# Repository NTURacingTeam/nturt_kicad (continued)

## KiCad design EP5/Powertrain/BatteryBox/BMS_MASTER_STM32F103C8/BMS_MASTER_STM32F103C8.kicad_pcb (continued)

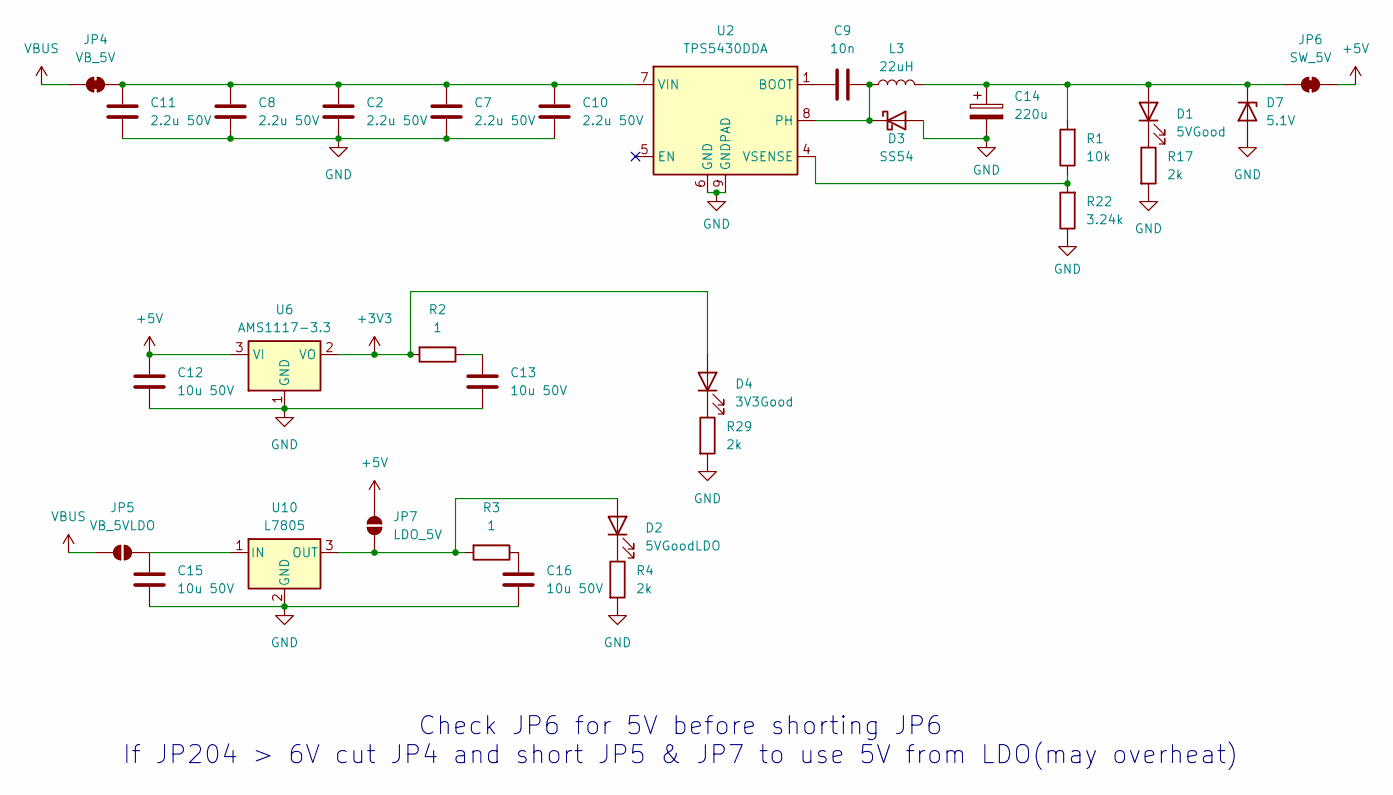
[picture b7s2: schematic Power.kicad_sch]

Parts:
C2, C7, C8, C10, C11: 2.2u 50V; C_0805_2012Metric
C9: 10n; C_0603_1608Metric
C12, C13, C15, C16: 10u 50V; C_1206_3216Metric
C14: 220u; CP_Elec_8x10.5
D1: 5VGood; LED_0603_1608Metric
D2: 5VGoodLDO; LED_0603_1608Metric
D3: SS54; D_SMA
D4: 3V3Good; LED_0603_1608Metric
D7: 5.1V; D_SOD-123
JP4: VB_5V; SolderJumper-2_P1.3mm_Bridged_Pad1.0x1.5mm
JP5: VB_5VLDO; SolderJumper-2_P1.3mm_Open_Pad1.0x1.5mm
JP6: SW_5V; SolderJumper-2_P1.3mm_Open_Pad1.0x1.5mm
JP7: LDO_5V; SolderJumper-2_P1.3mm_Open_Pad1.0x1.5mm
L3: 22uH; L_Bourns_SRR1260
R1: 10k; R_0603_1608Metric
R2, R3: 1; R_1206_3216Metric
R4, R17, R29: 2k; R_0603_1608Metric
R22: 3.24k; R_0603_1608Metric
U2: TPS5430DDA; TI_SO-PowerPAD-8_ThermalVias
U6: AMS1117-3.3; SOT-223-3_TabPin2
U10: L7805; TO-252-2

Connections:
3V3_REF: D4.2 (A), R2.2, U6.2 (VO); also elsewhere on the board
+5V: C12.1, JP6.2 (B), JP7.2 (B), U6.3 (VI); also elsewhere on the board
GND: C2.2, C7.2, C8.2, C10.2, C11.2, C12.2, C13.2, C14.2, C15.2, C16.2, D3.2 (A), D7.2 (A), R4.2, R17.2, R22.1, R29.2, U2.6 (GND), U2.9 (GNDPAD), U6.1 (GND), U10.2 (GND); also elsewhere on the board
unnamed: C13.1, R2.1
unnamed: C16.1, R3.1
unnamed: C14.1, D1.2 (A), D7.1 (K), JP6.1 (A), L3.2, R1.2
unnamed: D1.1 (K), R17.1
unnamed: D2.2 (A), JP7.1 (A), R3.2, U10.3 (OUT)
unnamed: D2.1 (K), R4.1
unnamed: C9.2, D3.1 (K), L3.1, U2.8 (PH)
unnamed: D4.1 (K), R29.1
unnamed: C2.1, C7.1, C8.1, C10.1, C11.1, JP4.2 (B), U2.7 (VIN)
unnamed: C15.1, JP5.2 (B), U10.1 (IN)
unnamed: C9.1, U2.1 (BOOT)
unnamed: R1.1, R22.2, U2.4 (VSENSE)
VBUS: JP4.1 (A), JP5.1 (A); also elsewhere on the board

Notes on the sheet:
Check JP6 for 5V before shorting JP6 If JP204 > 6V cut JP4 and short JP5 & JP7 to use 5V from LDO(may overheat)

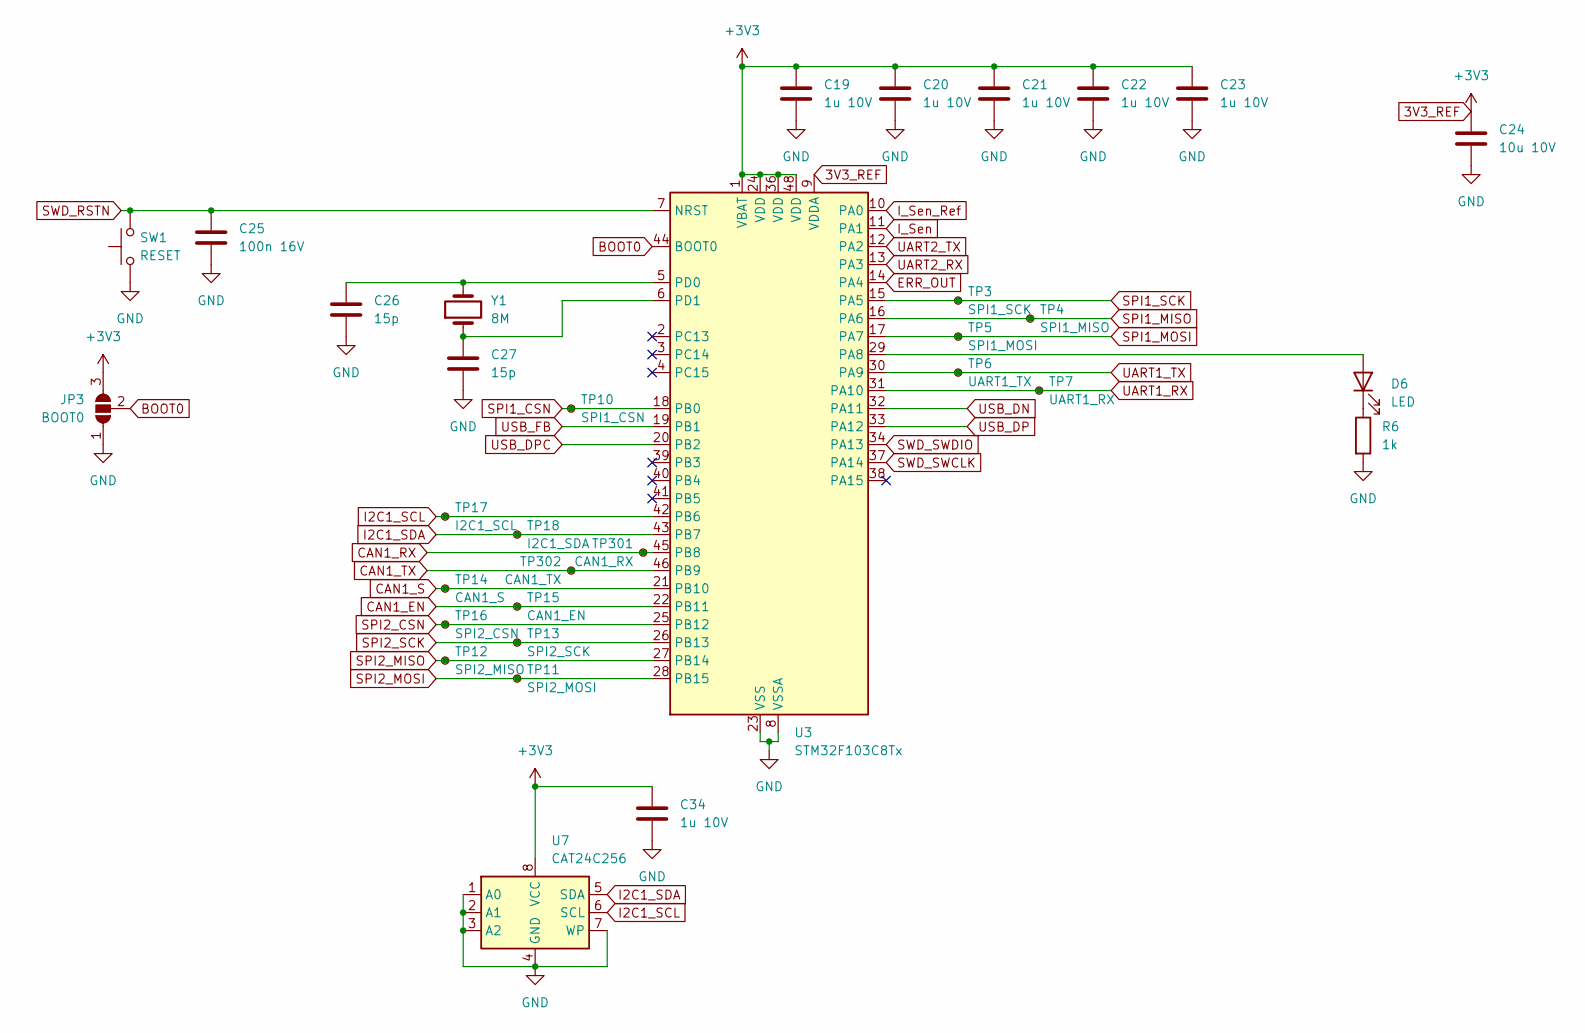
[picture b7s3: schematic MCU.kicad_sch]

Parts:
C19, C20, C21, C22, C23, C34: 1u 10V; C_0603_1608Metric
C24: 10u 10V; C_0603_1608Metric
C25: 100n 16V; C_0603_1608Metric
C26, C27: 15p; C_0603_1608Metric
D6: LED; LED_0603_1608Metric
JP3: BOOT0; SolderJumper-3_P1.3mm_Open_Pad1.0x1.5mm
R6: 1k; R_0603_1608Metric
SW1: RESET; SW_Push_1P1T_XKB_TS-1187A
TP3: SPI1_SCK; TestPoint_Pad_D1.0mm
TP4: SPI1_MISO; TestPoint_Pad_D1.0mm
TP5: SPI1_MOSI; TestPoint_Pad_D1.0mm
TP6: UART1_TX; TestPoint_Pad_D1.0mm
TP7: UART1_RX; TestPoint_Pad_D1.0mm
TP10: SPI1_CSN; TestPoint_Pad_D1.0mm
TP11: SPI2_MOSI; TestPoint_Pad_D1.0mm
TP12: SPI2_MISO; TestPoint_Pad_D1.0mm
TP13: SPI2_SCK; TestPoint_Pad_D1.0mm
TP14: CAN1_S; TestPoint_Pad_D1.0mm
TP15: CAN1_EN; TestPoint_Pad_D1.0mm
TP16: SPI2_CSN; TestPoint_Pad_D1.0mm
TP17: I2C1_SCL; TestPoint_Pad_D1.0mm
TP18: I2C1_SDA; TestPoint_Pad_D1.0mm
TP301: CAN1_RX; TestPoint_Pad_D1.0mm
TP302: CAN1_TX; TestPoint_Pad_D1.0mm
U3: STM32F103C8Tx; LQFP-48_7x7mm_P0.5mm
U7: CAT24C256; SOIC-8_3.9x4.9mm_P1.27mm
Y1: 8M; Crystal_SMD_TXC_7A-2Pin_5x3.2mm

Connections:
3V3_REF: C19.1, C20.1, C21.1, C22.1, C23.1, C24.1, C34.1, JP3.3 (B), U3.1 (VBAT), U3.9 (VDDA), U3.24 (VDD), U3.36 (VDD), U3.48 (VDD), U7.8 (VCC); also elsewhere on the board
BOOT0: JP3.2 (C), U3.44 (BOOT0)
CAN1_EN: TP15.1, U3.22 (PB11); also elsewhere on the board
CAN1_RX: TP301.1, U3.45 (PB8); also elsewhere on the board
CAN1_S: TP14.1, U3.21 (PB10); also elsewhere on the board
CAN1_TX: TP302.1, U3.46 (PB9); also elsewhere on the board
ERR_OUT: U3.14 (PA4); also elsewhere on the board
GND: C19.2, C20.2, C21.2, C22.2, C23.2, C24.2, C25.1, C26.1, C27.1, C34.2, JP3.1 (A), R6.2, SW1.1, U3.8 (VSSA), U3.23 (VSS), U3.35 (VSS), U3.47 (VSS), U7.1 (A0), U7.2 (A1), U7.3 (A2), U7.4 (GND), U7.7 (WP); also elsewhere on the board
I2C1_SCL: TP17.1, U3.42 (PB6), U7.6 (SCL)
I2C1_SDA: TP18.1, U3.43 (PB7), U7.5 (SDA)
I_Sen: U3.11 (PA1); also elsewhere on the board
I_Sen_Ref: U3.10 (PA0); also elsewhere on the board
unnamed: D6.2 (A), U3.29 (PA8)
unnamed: D6.1 (K), R6.1
unnamed: C26.2, U3.5 (PD0), Y1.2
unnamed: C27.2, U3.6 (PD1), Y1.1
SPI1_CSN: TP10.1, U3.18 (PB0); also elsewhere on the board
SPI1_MISO: TP4.1, U3.16 (PA6); also elsewhere on the board
SPI1_MOSI: TP5.1, U3.17 (PA7); also elsewhere on the board
SPI1_SCK: TP3.1, U3.15 (PA5); also elsewhere on the board
SPI2_CSN: TP16.1, U3.25 (PB12); also elsewhere on the board
SPI2_MISO: TP12.1, U3.27 (PB14); also elsewhere on the board
SPI2_MOSI: TP11.1, U3.28 (PB15); also elsewhere on the board
SPI2_SCK: TP13.1, U3.26 (PB13); also elsewhere on the board
SWD_RSTN: C25.2, SW1.2, U3.7 (NRST); also elsewhere on the board
SWD_SWCLK: U3.37 (PA14); also elsewhere on the board
SWD_SWDIO: U3.34 (PA13); also elsewhere on the board
UART1_RX: TP7.1, U3.31 (PA10); also elsewhere on the board
UART1_TX: TP6.1, U3.30 (PA9); also elsewhere on the board
UART2_RX: U3.13 (PA3); also elsewhere on the board
UART2_TX: U3.12 (PA2); also elsewhere on the board
USB_DN: U3.32 (PA11)
USB_DP: U3.33 (PA12)
USB_DPC: U3.20 (PB2)
USB_FB: U3.19 (PB1)

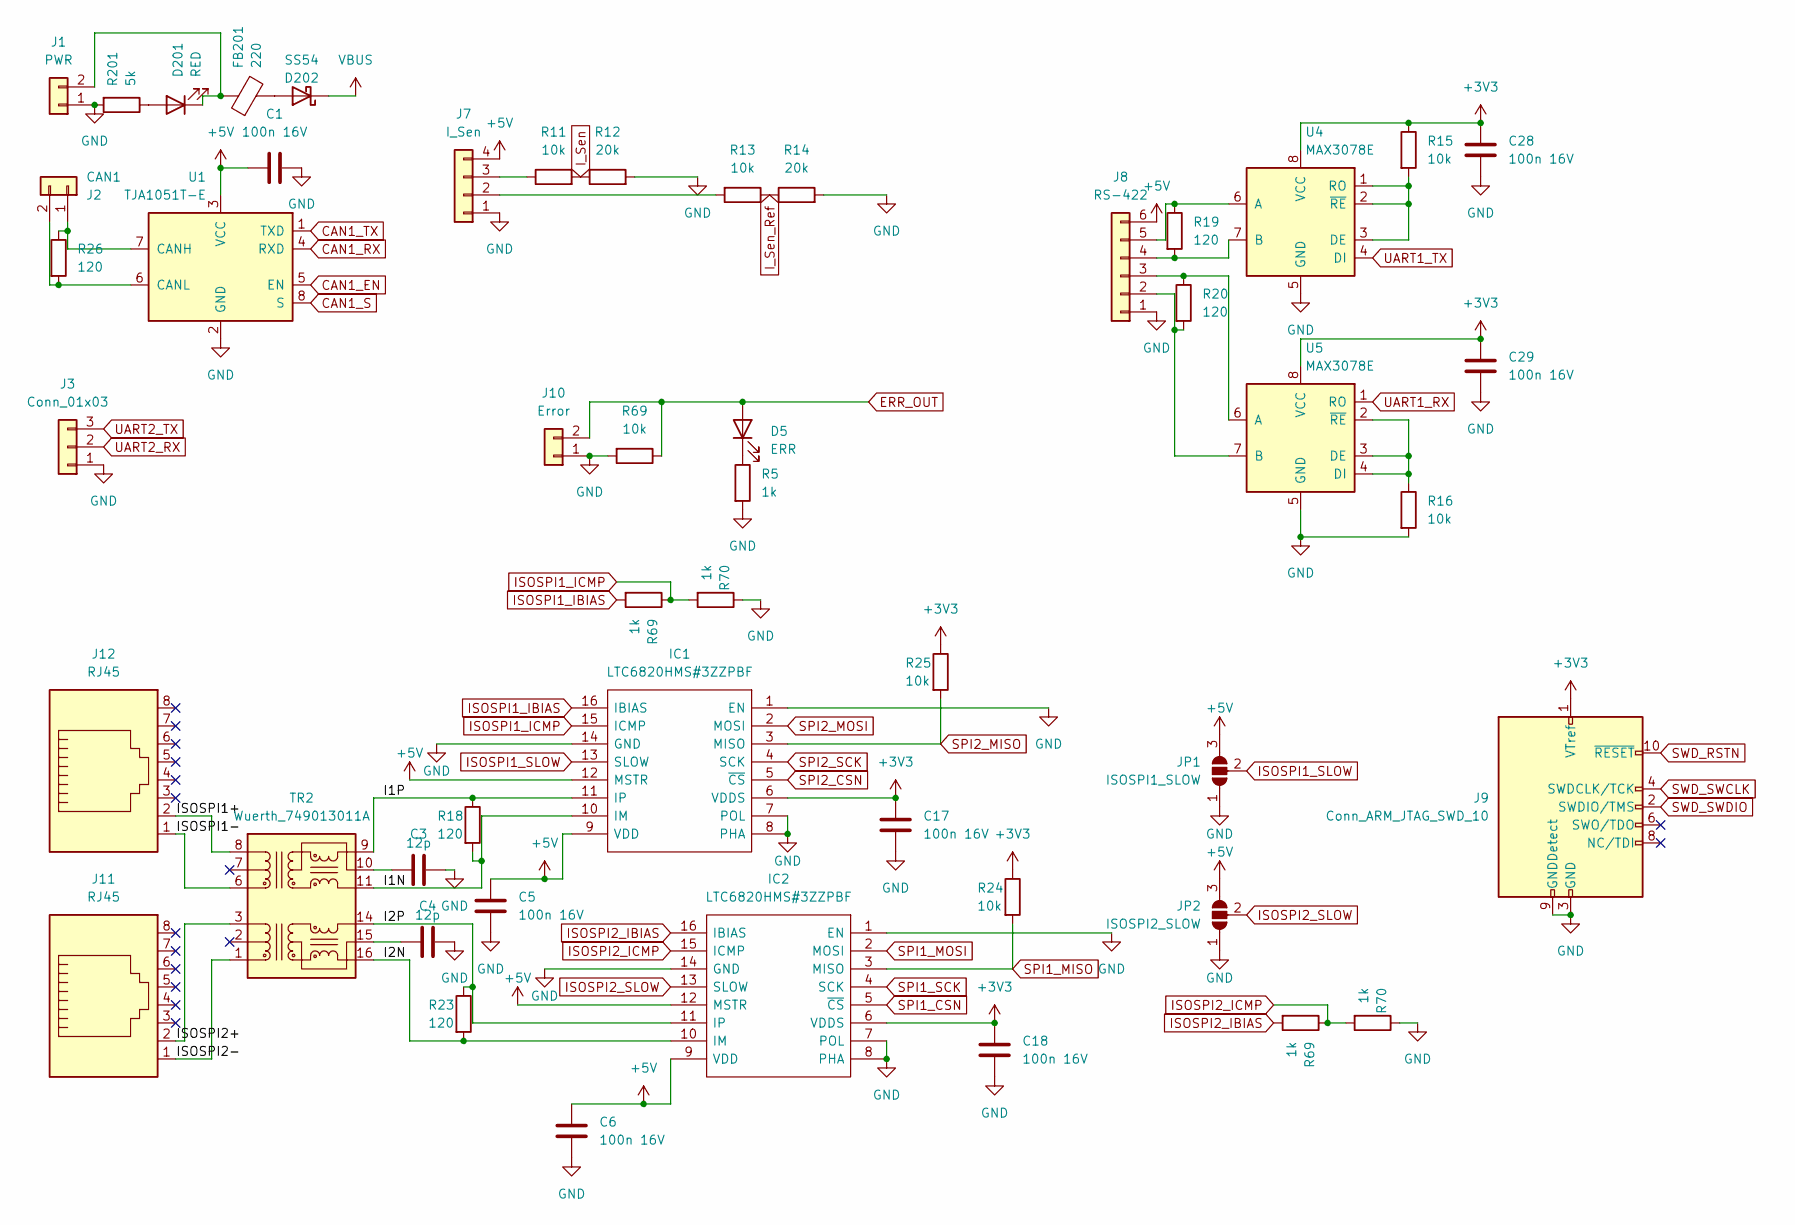
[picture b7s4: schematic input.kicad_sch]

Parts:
C1, C5, C6, C17, C18, C28, C29: 100n 16V; C_0603_1608Metric
C3, C4: 12p; C_0603_1608Metric
D5: ERR; LED_0603_1608Metric
D201: RED; LED_0603_1608Metric
D202: SS54; D_SMA
FB201: 220; R_0603_1608Metric
IC1, IC2: LTC6820HMS#3ZZPBF; SOP50P490X110-16N; Mouser Part Number 584-6820HMS#3ZZPB
J1: PWR; JST_XH_B2B-XH-A_1x02_P2.50mm_Vertical
J2: CAN1; JST_XH_B2B-XH-A_1x02_P2.50mm_Vertical
J3: Conn_01x03; JST_XH_B3B-XH-A_1x03_P2.50mm_Vertical
J7: I_Sen; JST_XH_B4B-XH-A_1x04_P2.50mm_Vertical
J8: RS-422; JST_XH_B6B-XH-A_1x06_P2.50mm_Vertical
J9: Conn_ARM_JTAG_SWD_10; PinHeader_2x05_P2.54mm_Vertical
J10: Error; JST_XH_B2B-XH-A_1x02_P2.50mm_Vertical
J11, J12: RJ45; RJ45_Amphenol_54602-x08_Horizontal
JP1: ISOSPI1_SLOW; SolderJumper-3_P1.3mm_Open_Pad1.0x1.5mm
JP2: ISOSPI2_SLOW; SolderJumper-3_P1.3mm_Open_Pad1.0x1.5mm
R5, R69, R70: 1k; R_0603_1608Metric
R11, R13, R15, R16, R24, R25: 10k; R_0603_1608Metric
R12, R14: 20k; R_0603_1608Metric
R18, R19, R20, R23, R26: 120; R_0603_1608Metric
R201: 5k; R_0603_1608Metric
TR2: Wuerth_749013011A; Transformer_Ethernet_Wuerth_749013011A
U1: TJA1051T-E; SOIC-8_3.9x4.9mm_P1.27mm
U4, U5: MAX3078E; SOIC-8_3.9x4.9mm_P1.27mm

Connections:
3V3_REF: C17.2, C18.2, C28.2, C29.2, IC1.6 (VDDS), IC2.6 (VDDS), J9.1 (VTref), R15.1, R24.1, R25.1, U4.8 (VCC), U5.8 (VCC); also elsewhere on the board
+5V: C1.1, C5.2, C6.2, IC1.9 (VDD), IC1.12 (MSTR), IC2.9 (VDD), IC2.12 (MSTR), J7.4, J8.6, JP1.3 (B), JP2.3 (B), U1.3 (VCC); also elsewhere on the board
/Input Stage/I1N: IC1.10 (IM), R18.2, TR2.11 (RX+)
/Input Stage/I1P: IC1.11 (IP), R18.1, TR2.9 (RX-)
/Input Stage/I2N: IC2.10 (IM), R23.2, TR2.16 (TX+)
/Input Stage/I2P: IC2.11 (IP), R23.1, TR2.14 (TX-)
/Input Stage/ISOSPI1+: J12.2, TR2.8 (RD-)
/Input Stage/ISOSPI1-: J12.1, TR2.6 (RD+)
/Input Stage/ISOSPI2+: J11.2, TR2.3 (TD-)
/Input Stage/ISOSPI2-: J11.1, TR2.1 (TD+)
CAN1_EN: U1.5 (EN); also elsewhere on the board
CAN1_RX: U1.4 (RXD); also elsewhere on the board
CAN1_S: U1.8 (S); also elsewhere on the board
CAN1_TX: U1.1 (TXD); also elsewhere on the board
ERR_OUT: D5.2 (A), J10.2; also elsewhere on the board
GND: C1.2, C3.2, C4.2, C5.1, C6.1, C17.1, C18.1, C28.1, C29.1, IC1.1 (EN), IC1.7 (POL), IC1.8 (PHA), IC1.14 (GND), IC2.1 (EN), IC2.7 (POL), IC2.8 (PHA), IC2.14 (GND), J1.1, J3.1, J7.1, J8.1, J9.3 (GND), J9.5 (GND), J9.9 (GNDDetect), J10.1, JP1.1 (A), JP2.1 (A), R5.2, R12.2, R14.2, R16.2, R201.2, U1.2 (GND), U4.5 (GND), U5.5 (GND); also elsewhere on the board
ISOSPI1_IBIAS: IC1.16 (IBIAS); also elsewhere on the board
ISOSPI1_ICMP: IC1.15 (ICMP); also elsewhere on the board
ISOSPI1_SLOW: IC1.13 (SLOW), JP1.2 (C)
ISOSPI2_IBIAS: IC2.16 (IBIAS); also elsewhere on the board
ISOSPI2_ICMP: IC2.15 (ICMP); also elsewhere on the board
ISOSPI2_SLOW: IC2.13 (SLOW), JP2.2 (C)
I_Sen: R11.2, R12.1; also elsewhere on the board
I_Sen_Ref: R13.1, R14.1; also elsewhere on the board
unnamed: D5.1 (K), R5.1
unnamed: D201.2 (A), R201.1
unnamed: D201.1 (K), FB201.1, J1.2
unnamed: D202.2 (A), FB201.2
unnamed: J2.1, R26.1, U1.7 (CANH)
unnamed: J2.2, R26.2, U1.6 (CANL)
unnamed: J7.2, R13.2
unnamed: J7.3, R11.1
unnamed: J8.2, R20.2, U5.7 (B)
unnamed: J8.3, R20.1, U5.6 (A)
unnamed: J8.4, R19.2, U4.7 (B)
unnamed: J8.5, R19.1, U4.6 (A)
unnamed: C3.1, TR2.10 (C_RX)
unnamed: C4.1, TR2.15 (C_TX)
unnamed: R15.2, U4.1 (RO), U4.2 (~RE), U4.3 (DE)
unnamed: R16.1, U5.2 (~RE), U5.3 (DE), U5.4 (DI)
SPI1_CSN: IC2.5 (~CS); also elsewhere on the board
SPI1_MISO: IC2.3 (MISO), R24.2; also elsewhere on the board
SPI1_MOSI: IC2.2 (MOSI); also elsewhere on the board
SPI1_SCK: IC2.4 (SCK); also elsewhere on the board
SPI2_CSN: IC1.5 (~CS); also elsewhere on the board
SPI2_MISO: IC1.3 (MISO), R25.2; also elsewhere on the board
SPI2_MOSI: IC1.2 (MOSI); also elsewhere on the board
SPI2_SCK: IC1.4 (SCK); also elsewhere on the board
SWD_RSTN: J9.10 (~RESET); also elsewhere on the board
SWD_SWCLK: J9.4 (SWDCLK/TCK); also elsewhere on the board
SWD_SWDIO: J9.2 (SWDIO/TMS); also elsewhere on the board
UART1_RX: U5.1 (RO); also elsewhere on the board
UART1_TX: U4.4 (DI); also elsewhere on the board
UART2_RX: J3.2; also elsewhere on the board
UART2_TX: J3.3; also elsewhere on the board
VBUS: D202.1 (K); also elsewhere on the board

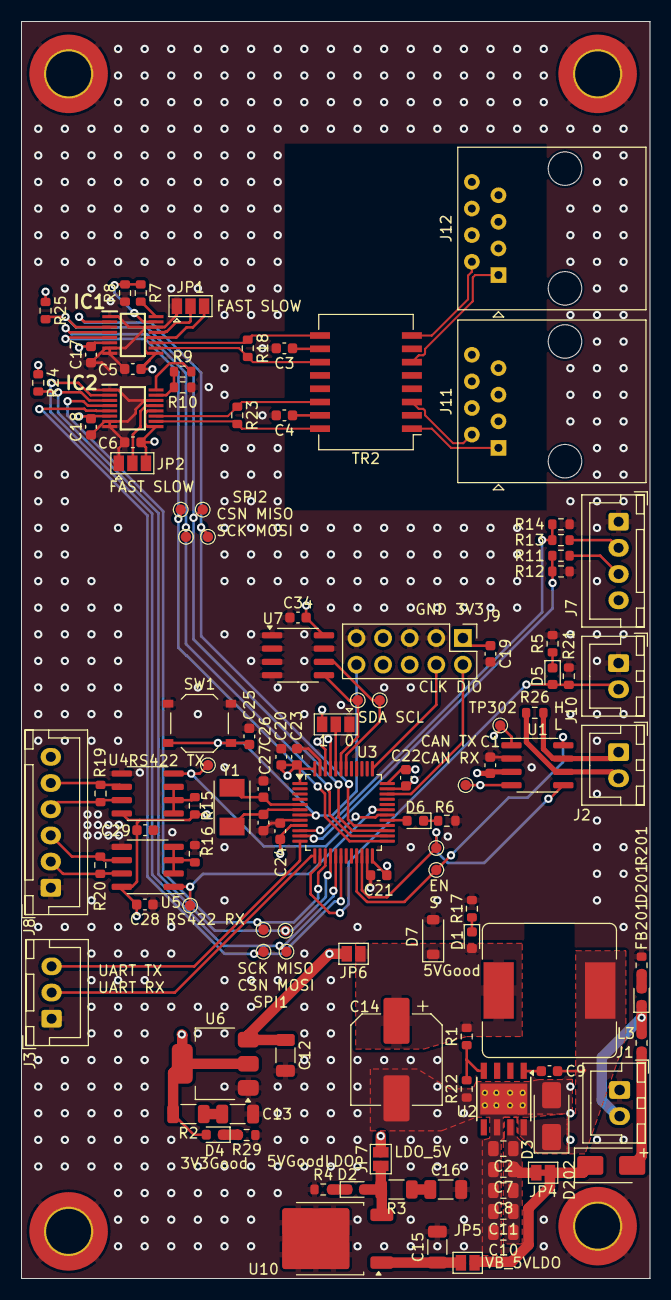
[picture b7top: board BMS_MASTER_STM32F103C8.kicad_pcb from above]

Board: 4 copper layers, 60.0 x 120.0 mm, 118 parts (0 on the bottom side), 75 nets.

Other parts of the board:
R7, R8, R9, R10: 1k; R_0603_1608Metric
R21: 10k; R_0603_1608Metric

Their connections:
ERR_OUT: R21.1; also elsewhere on the board
GND: R8.1, R10.1, R21.2; also elsewhere on the board
ISOSPI1_IBIAS: R7.2; also elsewhere on the board
ISOSPI1_ICMP: R7.1, R8.2; also elsewhere on the board
ISOSPI2_IBIAS: R9.2; also elsewhere on the board
ISOSPI2_ICMP: R9.1, R10.2; also elsewhere on the board
